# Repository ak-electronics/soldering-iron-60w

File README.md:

# 🔥 60W Soldering Iron – Custom PCB Project

This project contains the complete design files for a **60W Soldering Iron PCB**, made using **KiCad**.  
All project files — including **schematic**, **PCB layout**, and **Gerber files** — are available in this repository.

👉 Designed using KiCad
https://www.kicad.org/

👉 PCB manufactured by NextPCB
https://www.nextpcb.com/?code=HarGharManufacturing

👉 Source code & PCB files
https://github.com/ak-electronics/soldering-iron-60w

---

## 📌 Project Highlights

- ✔️ Designed using **KiCad**  
- ✔️ High-power **60W heater control**  
- ✔️ MOSFET-based driver  
- ✔️ Clean PCB layout for stable temperature operation  
- ✔️ Gerber files included  
- ✔️ Schematic & PCB source files included  

---

## 📁 Included Files

This repository contains:

- **Schematic (.sch)**
- **PCB Layout (.kicad_pcb)**
- **Gerber Files (Manufacturing-ready)**
- **BOM / Component list (if provided)**
- **3D View screenshots (optional)**

---

## 📺 YouTube Video Series

I created a 3-part YouTube Shorts series documenting the full process:

### **1️⃣ PCB Design using KiCad**
🔗 https://youtube.com/shorts/0d3w683Unvo?feature=share 

### **2️⃣ PCB Unboxing (NextPCB)**
🔗 https://youtube.com/shorts/kNqDfgHMU-M?feature=share  

### **3️⃣ PCB Assembly & Final Heat Test**
🔗 https://youtube.com/shorts/WlmB59tTTzk?feature=share  

---

## 🏭 PCB Manufacturing

This PCB was fabricated by **NextPCB**  
🔗 https://www.nextpcb.com/?code=HarGharManufacturing  

They offer fast and affordable PCB manufacturing — recommended if you want to build this project!

---

## 🛠️ Tools Used

- **KiCad PCB Design Software**  
  https://www.kicad.org/

- **NextPCB Manufacturing Service**  
  https://www.nextpcb.com/?code=HarGharManufacturing  

---

## 📬 Contact

If you have questions, suggestions, or collaboration ideas:

📧 **Email:** si.akash001@gmail.com

---

## ⭐ Support

If you like this project, feel free to **star ⭐ the repo** and watch the YouTube series to support the work!

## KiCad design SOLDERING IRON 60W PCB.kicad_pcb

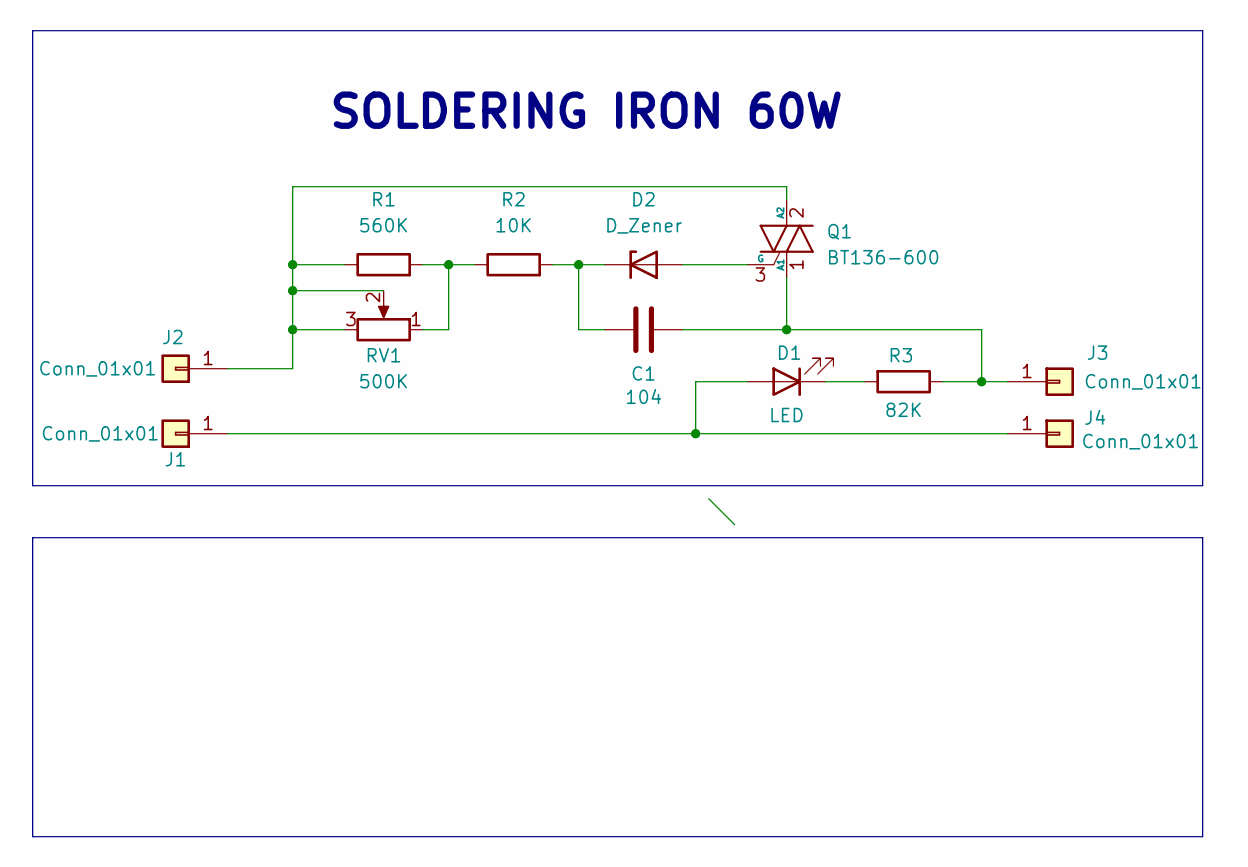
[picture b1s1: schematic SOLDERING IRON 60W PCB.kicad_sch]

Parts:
C1: 104; C_1206_3216Metric
D1: LED; LED_0805_2012Metric
D2: D_Zener; D_1206_3216Metric
J1, J2, J3, J4: Conn_01x01; Pin_D1.0mm_L10.0mm
Q1: BT136-600; TO-252-2
R1: 560K; R_1210_3225Metric
R2: 10K; R_1210_3225Metric
R3: 82K; R_1210_3225Metric
RV1: 500K; Potentiometer_Piher_PT-6-V_Vertical

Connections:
unnamed: D1.2 (A), J1.1, J4.1
unnamed: D1.1 (K), R3.2
unnamed: D2.2 (A), Q1.3 (G)
unnamed: C1.1, D2.1 (K), R2.2
unnamed: J2.1, Q1.2 (A2), R1.1, RV1.2, RV1.3
unnamed: C1.2, J3.1, Q1.1 (A1), R3.1
unnamed: R1.2, R2.1, RV1.1

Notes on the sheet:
SOLDERING IRON 60W

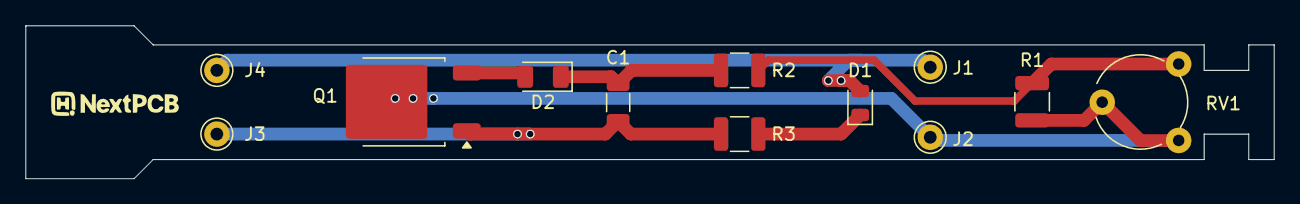
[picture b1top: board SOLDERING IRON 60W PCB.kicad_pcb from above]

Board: 2 copper layers, 98.0 x 12.0 mm, 12 parts (0 on the bottom side), 7 nets.

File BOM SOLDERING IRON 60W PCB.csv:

"Reference","Qty","Value","DNP","Exclude from BOM","Exclude from Board","Footprint","Datasheet"
"C1","1","104","","","","Capacitor_SMD:C_1206_3216Metric","~"
"D1","1","LED","","","","LED_SMD:LED_0805_2012Metric","~"
"D2","1","D_Zener","","","","Diode_SMD:D_1206_3216Metric","~"
"J1,J2,J3,J4","4","Conn_01x01","","","","Connector_Pin:Pin_D1.0mm_L10.0mm","~"
"Q1","1","BT136-600","","","","Package_TO_SOT_SMD:TO-252-2","http://www.micropik.com/PDF/BT136-600.pdf"
"R1","1","560K","","","","Resistor_SMD:R_1210_3225Metric","~"
"R2","1","10K","","","","Resistor_SMD:R_1210_3225Metric","~"
"R3","1","82K","","","","Resistor_SMD:R_1210_3225Metric","~"
"RV1","1","500K","","","","Potentiometer_THT:Potentiometer_Piher_PT-6-V_Vertical","~"

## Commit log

2025-11-29 First change v1.0.1
2025-11-29 Add project details for 60W Soldering Iron Controller
    Added detailed project information for a 60W soldering iron temperature controller, including features, working principles, BOM, safety notices, and getting started instructions.
2025-12-01 Enhance README with PCB manufacturing details
    Added PCB manufacturing section and updated title formatting.
2025-12-09 add gerber v1.1
2025-12-10 Add BOM and readme v1.3
2025-12-10 change in readme
